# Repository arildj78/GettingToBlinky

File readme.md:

# Getting to Blinky

This project is designed to introduce you to KiCad and electronics design. The gadget is battery powered and will blink a high luminosity LED as well as output a tone to a speaker. The frequency can be switched between 1 Hz and 440Hz with a solder jumper. The two integrated circuits are classics and are considered [jellybean](https://forum.digikey.com/t/what-are-jellybean-electronic-components/46180) parts.

## The schematic

## General design requirements
* Power supplied by [3 x AA batteries](https://www.digikey.no/en/products/detail/keystone-electronics/2464/303813)
* Generate the pulsed signal with a [555 timer](/datasheets/ne555.pdf) chip
* Boost the battery voltage with the [MC34063](/datasheets/MC34063A-D.pdf) DC-DC regulator
* Let the 555 timer drive 0.25 Watt into an 8Ω speaker without an additional amplifier
* Use only through hole parts in the design with two small exceptions
* Familiarize the designer with SMD parts of imperial size 0603 and 0805.
* Introduce some of the tools and techniques that are useful in KiCad
* Cut a slot in the PCB to use as strain relief for the speaker cable
* Use a two layer pcb design

## DC-DC regulator design decisions
* Input voltage 3.75V ±20%
    * An assumption is made that an alkaline cell with 50% of the energy left is at approximately 1.25V. We are using three of these in series.
* Output current 150mA
    * This is a compromise. Not all the way to 0.25 watt on the speaker and not maxing out the available current from the 555 timer chip. May change after prototyping.
* Output Voltage 6.25V
    * The voltage needs to be this high to get 2.4V voltage swing on the output when pulling 150mA from the output of the 555.
* Switching frequency 100kHz
    * A high switching frequency lets the inductor be small. This is the maximum frequency supported by the selected regulator.
* Output ripple voltage 100mV
    * An arbitrary value. Same as Dave chose in the YouTube video [EEVblog #110 - Let's Design a DC to DC Switch mode Converter](https://youtu.be/qGp82xhybs4).

## Teaching points in Schematic Editor
* Getting started with a new project i KiCad
* Placing parts and connecting them on the schematic
    * Place
    * Rotate
    * Mirror
    * Move
    * Grab
    * Wire
* Implementing the typical application found in the MC34063 and 555 datasheets
* Choosing component values from [E series of preferred numbers](https://en.wikipedia.org/wiki/E_series_of_preferred_numbers)
* Searching for parts on [DigiKey](https://digikey.com), [JLCPCB](https://jlcpcb.com/parts) and [LCSC](https://www.lcsc.com/)
* Choosing footprints
* Adding symbol data by using *fields* and the *Symbol Fields Table*
* Using the *Do not populate* and *Exclude from Bill Of Materials* (BOM) option
* The purpose of the 0.1µF decoupling capacitor
* Dividing a schematic into functional blocks
* Annotating the schematic
* Running Electrical Rules Check

## Teaching points in PCB Editor
* Switching from schematic to pcb
* Update PCB from schematic
* Move components into functional blocks
* Untangle the ratsnest
* Draw board outline
* Pre-define sizes for tracks and vias.
    * 0.3mm (0.012") track
    * 0.7mm (0.028") track
    * 1.0mm / 0.4mm via
* Route Tracks
    * Track size
    * Use of vias and multiple layers
* Create filled zones for ground (and power if the board had more layers)
* Use the 3D-viewer
* Use the Design Rules Check

## Suggested Parts list
|Reference |Value    |Manufacturer               |Part#             |DigiKey#                   |Qty|
|----------|---------|---------------------------|------------------|---------------------------|---|
|BT1       |Battery  |Keystone Electronics       |2464              |36-2464-ND                 |  1|
|C1,C2     |100u     |Chinsan (Elite)            |ED1E101MP26311U   |4191-ED1E101MP26311UCT-ND  |  2|
|C3        |22u      |Murata Electronics         |GRM188C61E226ME01J|490-GRM188C61E226ME01JCT-ND|  1|
|C4,C7     |470u     |Chinsan (Elite)            |EK1C471MP30812    |4191-EK1C471MP30812CT-ND   |  2|
|C5        |1u       |TDK Corporation            |FG24X7R1H105KRT06 |445-173374-1-ND            |  1|
|C6        |0.1u     |KEMET                      |C320C104M5R5TA    |399-9776-ND                |  1|
|Ct1       |240p     |KEMET                      |C318C241K3G5TA    |C318C241K3G5TA-ND          |  1|
|D1        |1N5819   |STMicroelectronics         |1N5819            |497-6610-1-ND              |  1|
|D2        |Green    |Inolux                     |INL-5AG30         |1830-1011-ND               |  1|
|L1        |15u      |Bourns Inc.                |RLB0913-150K      |RLB0913-150K-ND            |  1|
|R1,R4     |180      |Stackpole Electronics Inc  |CF14JT180R        |CF14JT180RCT-ND            |  2|
|R2        |64k9     |YAGEO                      |MFR-25FRF52-64K9  |13-MFR-25FRF52-64K9CT-ND   |  1|
|R3        |16k2     |YAGEO                      |MFR-25FTE52-16K2  |13-MFR-25FTE52-16K2CT-ND   |  1|
|R5        |1k5      |YAGEO                      |MFR-25FTF52-1K5   |13-MFR-25FTF52-1K5CT-ND    |  1|
|R6        |75       |Stackpole Electronics Inc  |CF14JT75R0        |CF14JT75R0CT-ND            |  1|
|R7        |8.06     |KOA Speer Electronics, Inc.|RK73H2ATTD8R06F   |2019-RK73H2ATTD8R06FCT-ND  |  1|
|Rsc1      |240m     |YAGEO                      |MFR-25JR-52-0R24  |13-MFR-25JR-52-0R24CT-ND   |  1|
|U1        |MC34063AP|onsemi                     |MC34063AP1G       |MC34063AP1GOS-ND           |  1|
|U2        |NE555P   |Texas Instruments          |NE555P            |296-NE555P-ND              |  1|

## Suggested Footprints
|Reference             |Footprint                                                     |
|----------------------|--------------------------------------------------------------|
|BT1                   |Battery:BatteryHolder_TruPower_BH-331P_3xAA                   |
|C1,C2                 |Capacitor_THT:CP_Radial_D6.3mm_P2.50mm                        |
|C3                    |Capacitor_SMD:C_0603_1608Metric_Pad1.08x0.95mm_HandSolder     |
|C4,C7                 |Capacitor_THT:CP_Radial_D8.0mm_P3.50mm                        |
|C5                    |Capacitor_THT:C_Disc_D5.1mm_W3.2mm_P5.00mm                    |
|C6                    |Capacitor_THT:C_Disc_D5.0mm_W2.5mm_P2.50mm                    |
|Ct1                   |Capacitor_THT:C_Rect_L7.0mm_W3.5mm_P5.00mm                    |
|D1                    |Diode_THT:D_DO-41_SOD81_P10.16mm_Horizontal                   |
|D2                    |LED_THT:LED_D5.0mm                                            |
|L1                    |Inductor_THT:L_Radial_D8.7mm_P5.00mm_Fastron_07HCP            |
|R1,R2,R3,R4,R5,R6,Rsc1|Resistor_THT:R_Axial_DIN0207_L6.3mm_D2.5mm_P10.16mm_Horizontal|
|R7                    |Resistor_SMD:R_0805_2012Metric_Pad1.20x1.40mm_HandSolder      |
|U1,U2                 |Package_DIP:DIP-8_W7.62mm                                     |

## Reference material
* [EEVblog #110 - Let's Design a DC to DC Switch mode Converter](https://youtu.be/qGp82xhybs4)

## Useful tools
* [KiCad](https://www.kicad.org/)
* [LTspice circuit simulator](https://www.analog.com/en/resources/design-tools-and-calculators/ltspice-simulator.html)
* [Saturn PCB Design Toolkit](https://saturnpcb.com/saturn-pcb-toolkit/)
* [Resistor calculator](https://damien.douxchamps.net/elec/resdiv/)

## Useful web services
* [jlcpcb.com](https://jlcpcb.com/)
* [digikey.com](https://www.digikey.com)
* [lcsc.com](https://www.lcsc.com/)
* [Falstad circuit simulator](https://www.falstad.com/circuit/circuitjs.html)

## My favorite podcasts
* [The Amp Hour](https://theamphour.com/)
* [Embedded FM](https://embedded.fm/)
* [Hackaday](https://hackaday.com/tag/hackaday-podcast/)
* [The Unnamed Reverse Engineering Podcast](https://unnamedre.com/)

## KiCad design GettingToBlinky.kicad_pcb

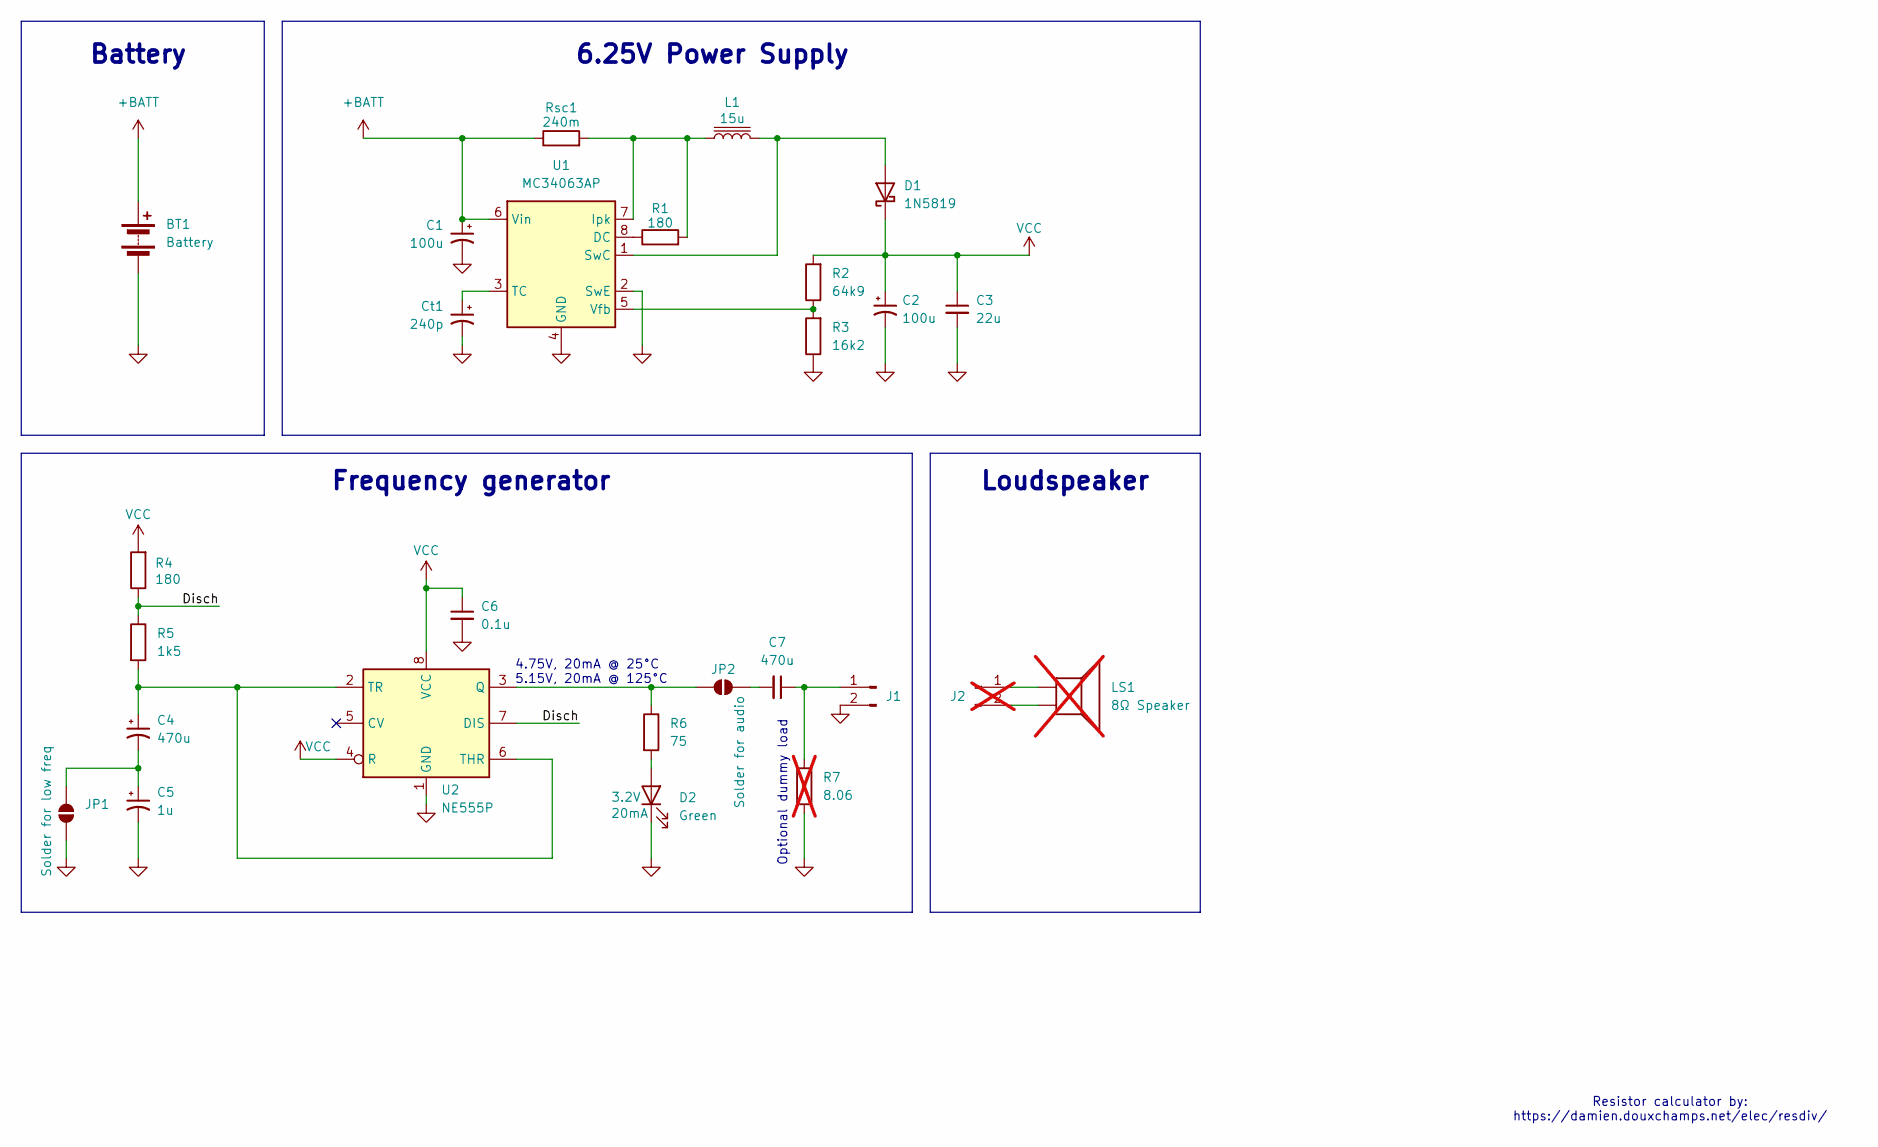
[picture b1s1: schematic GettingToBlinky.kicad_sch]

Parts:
BT1: Battery; BatteryHolder_TruPower_BH-331P_3xAA; Part# 2464; DigiKey# 36-2464-ND
C1, C2: 100u; CP_Radial_D6.3mm_P2.50mm; Part# ED1E101MP26311U; DigiKey# 4191-ED1E101MP26311UCT-ND
C3: 22u; C_0603_1608Metric_Pad1.08x0.95mm_HandSolder; Part# GRM188C61E226ME01J; DigiKey# 490-GRM188C61E226ME01JCT-ND
C4, C7: 470u; CP_Radial_D8.0mm_P3.50mm; Part# EK1C471MP30812; DigiKey# 4191-EK1C471MP30812CT-ND
C5: 1u; C_Disc_D5.1mm_W3.2mm_P5.00mm; Part# FG24X7R1H105KRT06; DigiKey# 445-173374-1-ND
C6: 0.1u; C_Disc_D5.0mm_W2.5mm_P2.50mm; Part# C320C104M5R5TA; DigiKey# 399-9776-ND
Ct1: 240p; C_Rect_L7.0mm_W3.5mm_P5.00mm; Part# C318C241K3G5TA; DigiKey# C318C241K3G5TA-ND
D1: 1N5819; D_DO-41_SOD81_P10.16mm_Horizontal; Part# 1N5819; DigiKey# 497-6610-1-ND
D2: Green; LED_D5.0mm; Part# INL-5AG30; DigiKey# 1830-1011-ND
J1: Conn_01x02_Pin; PinHeader_1x02_P2.54mm_Vertical
J2: Conn_01x02_Pin; PinHeader_1x02_P2.54mm_Vertical; not fitted
JP1: Solder for low freq; SolderJumper-2_P1.3mm_Open_RoundedPad1.0x1.5mm
JP2: Solder for audio; SolderJumper-2_P1.3mm_Open_RoundedPad1.0x1.5mm
L1: 15u; L_Radial_D8.7mm_P5.00mm_Fastron_07HCP; Part# RLB0913-150K; DigiKey# RLB0913-150K-ND
LS1: 8Ω Speaker; not fitted
R1, R4: 180; R_Axial_DIN0207_L6.3mm_D2.5mm_P10.16mm_Horizontal; Part# CF14JT180R; DigiKey# CF14JT180RCT-ND
R2: 64k9; R_Axial_DIN0207_L6.3mm_D2.5mm_P10.16mm_Horizontal; Part# MFR-25FRF52-64K9; DigiKey# 13-MFR-25FRF52-64K9CT-ND
R3: 16k2; R_Axial_DIN0207_L6.3mm_D2.5mm_P10.16mm_Horizontal; Part# MFR-25FTE52-16K2; DigiKey# 13-MFR-25FTE52-16K2CT-ND
R5: 1k5; R_Axial_DIN0207_L6.3mm_D2.5mm_P10.16mm_Horizontal; Part# MFR-25FTF52-1K5; DigiKey# 13-MFR-25FTF52-1K5CT-ND
R6: 75; R_Axial_DIN0207_L6.3mm_D2.5mm_P10.16mm_Horizontal; Part# CF14JT75R0; DigiKey# CF14JT75R0CT-ND
R7: 8.06; R_0805_2012Metric_Pad1.20x1.40mm_HandSolder; Part# RK73H2ATTD8R06F; DigiKey# 2019-RK73H2ATTD8R06FCT-ND; not fitted
Rsc1: 240m; R_Axial_DIN0207_L6.3mm_D2.5mm_P10.16mm_Horizontal; Part# MFR-25JR-52-0R24; DigiKey# 13-MFR-25JR-52-0R24CT-ND
U1: MC34063AP; DIP-8_W7.62mm; Part# MC34063AP1G; DigiKey# MC34063AP1GOS-ND
U2: NE555P; DIP-8_W7.62mm; Part# NE555P; DigiKey# 296-NE555P-ND

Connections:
+BATT: BT1.1 (+), C1.1, Rsc1.1, U1.6 (Vin)
/Disch: R4.1, R5.1, U2.7 (DIS)
GND: BT1.2 (-), C1.2, C2.2, C3.2, C5.2, C6.2, Ct1.2, D2.1 (K), J1.2, JP1.1 (A), R3.1, R7.2, U1.2 (SwE), U1.4 (GND), U2.1 (GND)
unnamed: D1.2 (A), L1.2, U1.1 (SwC)
unnamed: D2.2 (A), R6.2
unnamed: C7.1, J1.1, R7.1
unnamed: J2.1, LS1.1
unnamed: J2.2, LS1.2
unnamed: C4.2, C5.1, JP1.2 (B)
unnamed: C7.2, JP2.1 (A)
unnamed: JP2.2 (B), R6.1, U2.3 (Q)
unnamed: R1.1, U1.8 (DC)
unnamed: L1.1, R1.2, Rsc1.2, U1.7 (Ipk)
unnamed: Ct1.1, U1.3 (TC)
unnamed: R2.1, R3.2, U1.5 (Vfb)
unnamed: C4.1, R5.2, U2.2 (TR), U2.6 (THR)
VCC: C2.1, C3.1, C6.1, D1.1 (K), R2.2, R4.2, U2.4 (R), U2.8 (VCC)

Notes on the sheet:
4.75V, 20mA @ 25°C 5.15V, 20mA @ 125°C
Resistor calculator by: https://damien.douxchamps.net/elec/resdiv/
6.25V Power Supply
Optional dummy load
Loudspeaker
Battery
Frequency generator

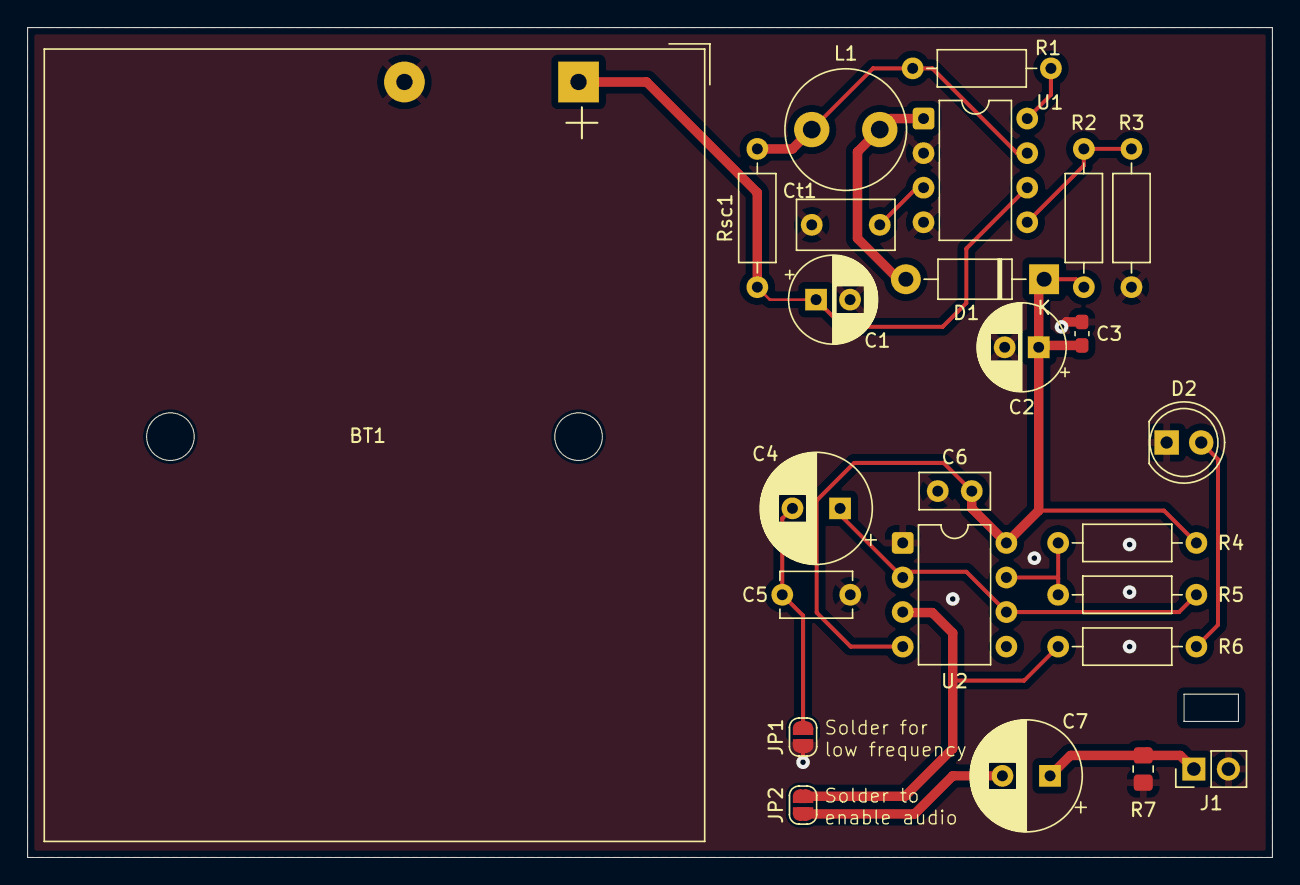
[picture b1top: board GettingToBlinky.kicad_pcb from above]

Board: 2 copper layers, 91.5 x 61.0 mm, 25 parts (0 on the bottom side), 15 nets.

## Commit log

2025-03-10 Fix of link to picture
2025-03-10 Second attempt at fixing link
2025-03-11 Moved individual gerber files into separate folder
2025-03-11 Renamed the board file to Rev A. This lets the user start with a blank sheet when entering the PCB editor.
2025-03-11 Corrected name of Electrical Rules Check
2025-03-11 Small correction
2025-03-11 Editorial changes
2025-03-11 Fixed broken links
2025-03-11 Added design decisions and image of the schematic
